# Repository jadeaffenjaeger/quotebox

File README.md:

## Quotebox

This piece of electronics was made for an installation where speakers at various places would play short bits of sound at random intervals. Since there was no power available, the speakers need to run off 1S LiPo batteries. Since the budget was quite low, only cheap and easy to source components were used.

### Components
A DFPlayer mini module is used to play mp3 sound bites from an SD card. Since the Idle Power consumption of the DFPlayer is quite high, even when in Standby mode, an external STM8 microcontroller is used to power up the DFPlayer through a MOSFET when needed and power it down as soon as it has finished playing. The STM8 also keeps track of sleep times and which track on the card to play next.
The components used are:
- [DFPlayer Mini](https://wiki.dfrobot.com/DFPlayer_Mini_SKU_DFR0299)
- [STM8S103 Breakout Board](https://github.com/TG9541/stm8ef/wiki/Breakout-Boards#stm8s103f3p6-breakout-board)
- [IRLZ44N MOSFET](http://www.irf.com/product-info/datasheets/data/irlz44n.pdf)
- [HobbyKing 1S 750mAh LiPo](https://hobbyking.com/en_us/turnigy-nano-tech-750mah-1s-35-70c-lipo-pack-fits-nine-eagles-solo-pro-180.html)
summing up to below 5€ per speaker (without battery)

### Energy
750mAh LiPo batteries from HobbyKing were used to power each speaker as I had them laying around from my drone anyway. Both the STM8 and DFPlayer work with 3-5V, so no voltage regulator was needed, keeping the price down. The voltage of the LiPo is not checked by the microcontroller, however, so the circuit will deep-discharge the battery if left unattended for too long. For our use case, the speakers played a sound of ca. 5s every few minutes. The STM8 needs ca. 2mA when in sleep mode (mostly
due to the power LED on the breakout board. If lower consumption is required, one should remove the LED). The DFPlayer consumes 50-120mA when playing a file (depending on the content of the file). All in all, the speakers would have been able to work for 2-3 days on a single LiPo.

### Firmware
The firmware for the STM8 is in the `src` folder. The DFPlayer is addressed over UART via the `dfplayer.c` module, the `awu.c` sends the microcontroller to sleep and the external MOSFET that powers the DFPlayer on and off is switched in the `gpio.c` file, along with the user LED.
The firmware can be built with SDCC using `make all` and uploaded to a board with `make flash`. An STLink (clone) and [stm8flash] are required for this. If you run into problems uploading to a new board, you might try unlocking it using `make unlock`

[stm8flash]: https://github.com/vdudouyt/stm8flash

### Schematics
I tried started doing a custom PCB for the speakers, but ended up opting for Perf Board eventually. The PCB layout therefore is not up to date and should not be used as is.

### Housing

Again, to keep cost low, the speakers were hot-glued into old CD-R spindles to give them some protection and improve the resonance of the speaker

### Summary
The speakers at full volume were loud enough to be heard indoors. The ones installed outdoors (in a rather noisy environment) were quite hard understand from a few meters away already, so a bigger speaker and amp would be required for this to work.

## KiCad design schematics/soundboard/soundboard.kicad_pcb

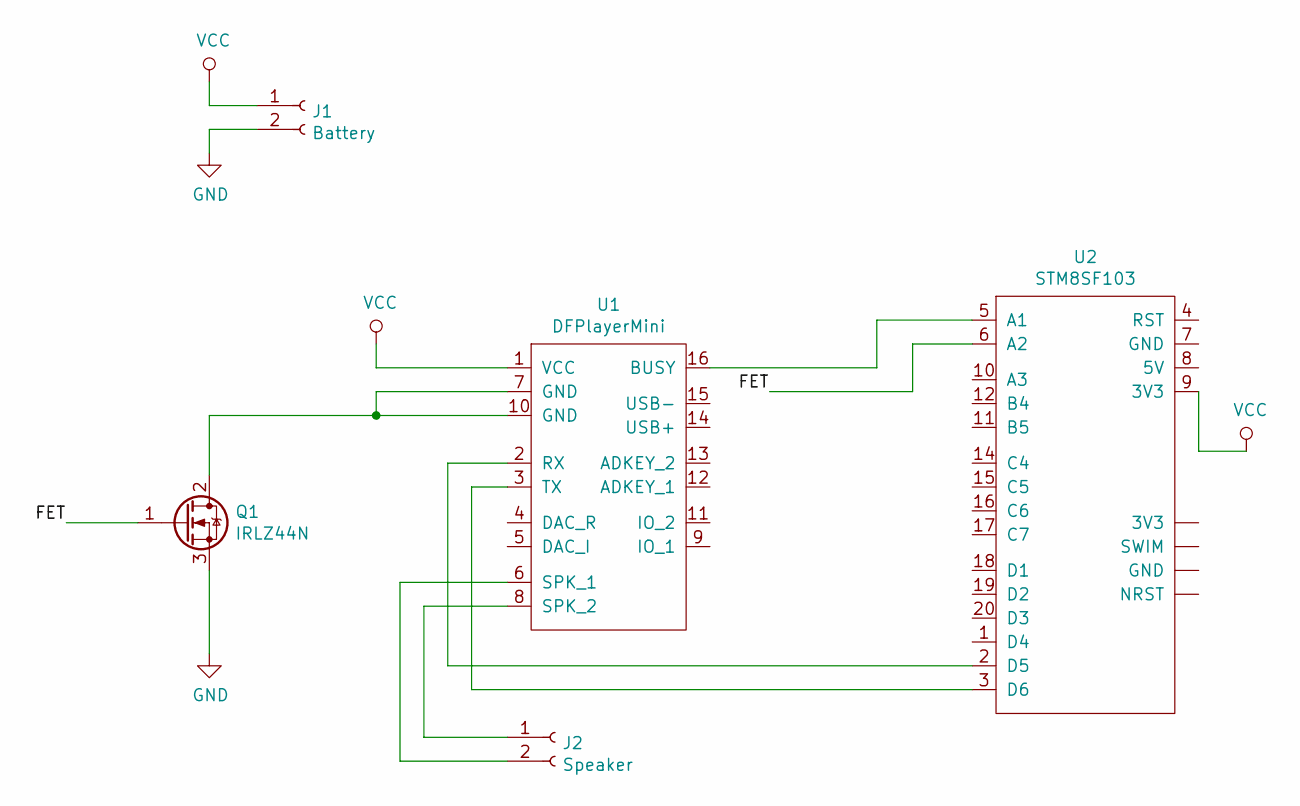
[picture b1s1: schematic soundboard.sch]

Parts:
J1: Battery; PinHeader_1x02_P2.54mm_Vertical
J2: Speaker; PinHeader_1x02_P2.54mm_Vertical
Q1: IRLZ44N; TO-220-3_Vertical
U1: DFPlayerMini; DFPlayer
U2: STM8SF103; STM8S103

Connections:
/FET: Q1.1 (G), U2.6 (A2)
GND: J1.2, Q1.3 (S)
unnamed: J2.1, U1.8 (SPK_2)
unnamed: J2.2, U1.6 (SPK_1)
unnamed: Q1.2 (D), U1.7 (GND), U1.10 (GND)
unnamed: U1.2 (RX), U2.2 (D5)
unnamed: U1.3 (TX), U2.3 (D6)
unnamed: U1.16 (BUSY), U2.5 (A1)
VCC: J1.1, U1.1 (VCC), U2.9 (3V3)

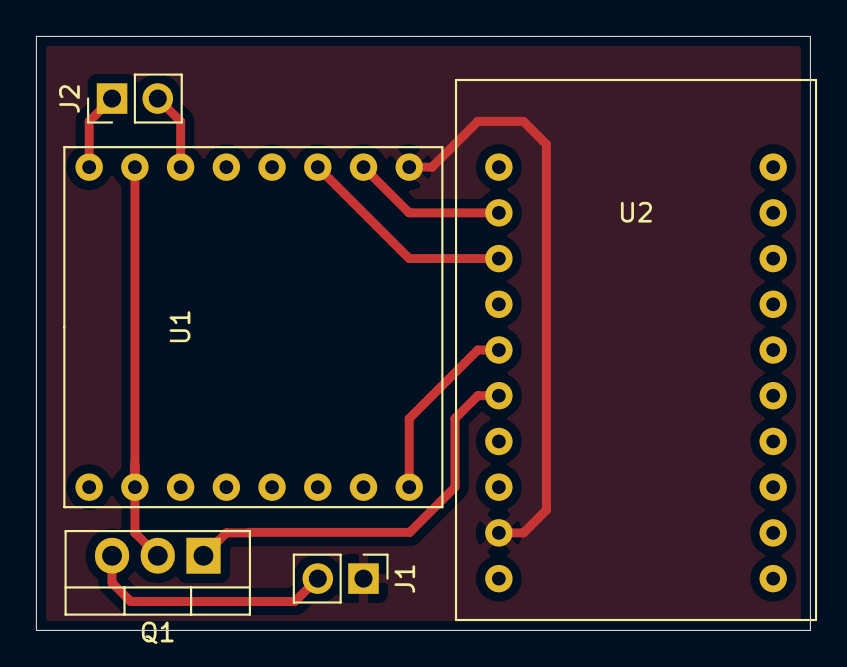
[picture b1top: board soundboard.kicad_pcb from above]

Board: 2 copper layers, 43.0 x 33.0 mm, 5 parts (0 on the bottom side), 9 nets.

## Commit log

2019-03-24 Reduce Clock speed and enable AWU
2019-03-28 Refactor AWU code
2019-04-14 Add 100ms interval to AWU
2019-04-14 Set system frequency to 16MHz
2019-04-14 WIP: Get track count from player
2019-04-14 Move GPIO to separate file
2019-04-19 Working Data retrieval and DFPlayer replay
2019-04-21 Add MOSFET control to GPIO
2019-04-21 Enable and disable Player via external MOSFET
2019-04-21 Add function to wait for DFPlayer to come up
2019-04-22 Add gitignore for KiCad files
2019-04-22 Add board schematics
2019-04-22 Add filled zone and outlines
2019-04-28 Change Pin mappings for FET and add BUSY pin
2019-04-29 Add convenience function for n seconds to AWU
2019-04-29 Change mapping of FET to PD4
2019-04-29 Implement working version in main
2019-05-03 Add array of idle times ans refactor
2019-05-06 Add 8bit LFSR implementation
2019-05-06 Add non-testing sleep times to main
2019-05-06 Fix compiler warnings
2019-05-06 remove underscores from LFSR include guard
2019-08-01 Add project details to README
2019-08-01 Add pictures
2019-08-01 Update FET pin in schematic
2019-08-01 Add schematic as PDF
2019-08-01 Add note about outdated PCB layout
2019-08-01 Add component information to README
